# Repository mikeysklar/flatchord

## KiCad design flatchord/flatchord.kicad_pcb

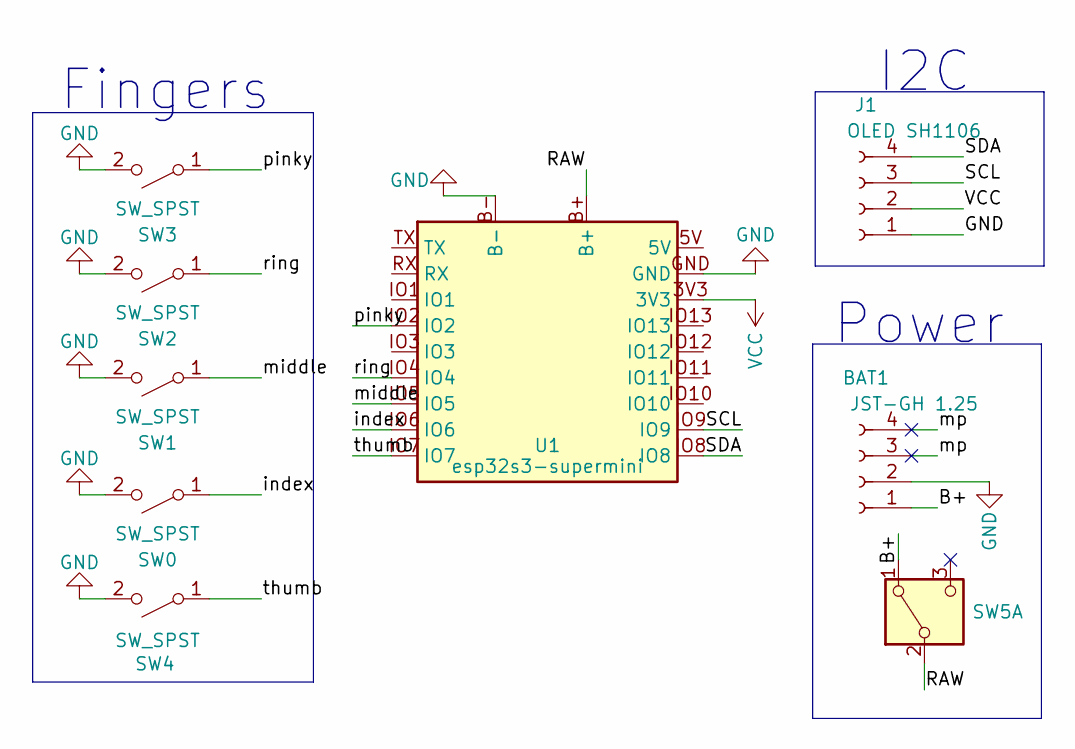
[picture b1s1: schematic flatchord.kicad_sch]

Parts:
BAT1: JST-GH 1.25; JST_GH_SM02B-GHS-TB_1x02-1MP_P1.25mm_Horizontal
J1: OLED SH1106; tft-sh1106-1.3-i2c
SW0, SW1, SW2, SW3, SW4: SW_SPST; Panasonic_EVQPUL_EVQPUC
SW5: SW_DPDT_x2; Untitled
U1: esp32s3-supermini; ESP32-S3-SuperMini_SMT

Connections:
/B+: BAT1.1, SW5.1 (A)
/RAW: SW5.2 (B), U1.B+
/SCL: J1.3, U1.IO9
/SDA: J1.4, U1.IO8
/index: SW0.1 (A), U1.IO6
/middle: SW1.1 (A), U1.IO5
/mp: BAT1.3, BAT1.4
/pinky: SW3.1 (A), U1.IO2
/ring: SW2.1 (A), U1.IO4
/thumb: SW4.1 (A), U1.IO7
GND: BAT1.2, J1.1, SW0.2 (B), SW1.2 (B), SW2.2 (B), SW3.2 (B), SW4.2 (B), U1.B-, U1.GND
VCC: J1.2, U1.3V3

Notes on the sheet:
Fingers
I2C
Power

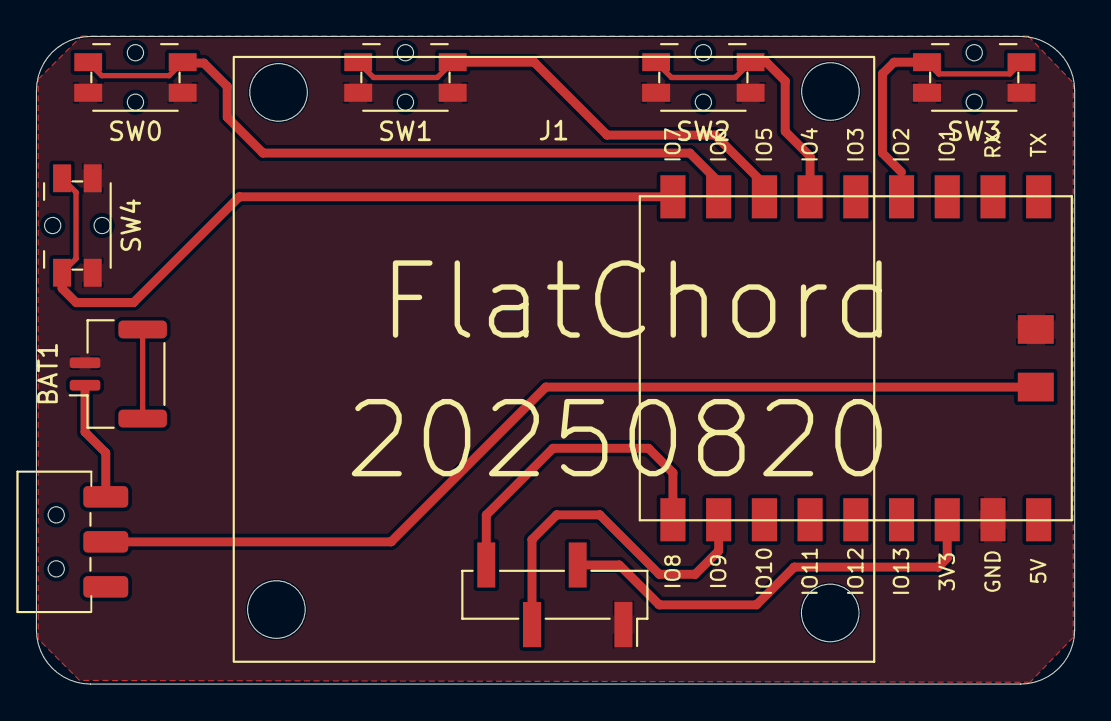
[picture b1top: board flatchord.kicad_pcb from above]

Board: 2 copper layers, 57.7 x 36.0 mm, 9 parts (0 on the bottom side), 12 nets.

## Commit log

2025-08-03 sch done / pcb started
2025-08-04 named board
2025-08-07 working PCB
    making the case
2025-08-07 case structure up
    very organized spreadsheet with comments.
2025-08-08 first case draft done
2025-08-10 2nd case print
    Good fit and works. Minor adjustments added to tighten up button fit. There is a slight wiggle.
2025-08-10 working keypad
    entering chars, looks good on screen
2025-08-10 added title in yellow
    text in blue below
2025-08-17 switch to esp32-s3 supermini
2025-08-19 significant changes
    new display 1.3" SH1106 and ESP32-S3 supermini, big shrink in size
2025-08-20 getting small
2025-08-20 ready for prototypes
2025-08-20 ready to fab
2025-08-22 taller not smaller
    needed to really boost the height based on pre-soldered male header on TFT. keeps it all SMT otherwise. Board passes all basic checks (charge, keys, tft) chord code needs work to display chars.
2025-08-22 chording works
2025-08-22 works well for 20 char display
2025-08-23 adding in save / scroll features
2025-08-23 getting saved entries now
2025-08-23 view history
    page up/down works for scrolling history
2025-08-23 interscroll arrow key view mode
2025-08-23 flipped display works
    180 rotation
2025-08-23 working with scroll feature
2025-08-23 case mods for better fit
    new big pink thumb
